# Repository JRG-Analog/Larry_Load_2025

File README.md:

# Larry_Load_2025
A current load for testing, named for the great Larry Carr, his original design.

This document describes the assembly, design, calibration and usage of “Larry Load”, a battery-powered, high accuracy current sink. The system consists of a small PCB inside and enclosure, with various panel mount components and connector mounted components to make a complete circuit.

PCB Layout is shared on OSHPark.com as LL Basic 2025.kicad_pcb

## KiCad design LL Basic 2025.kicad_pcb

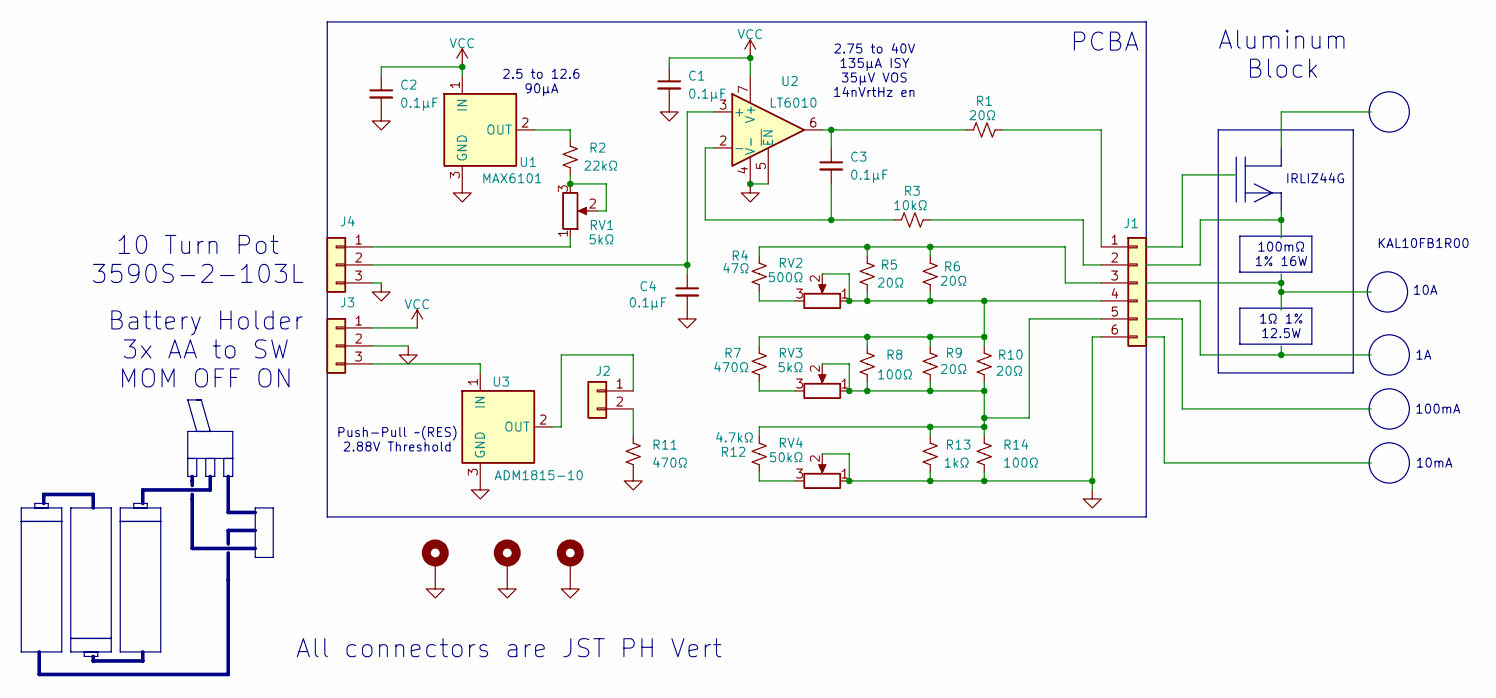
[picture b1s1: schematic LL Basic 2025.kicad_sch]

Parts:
C1, C2, C3, C4: 0.1µF; C_Rect_L4.0mm_W2.5mm_P2.50mm
H1, H2, H3: MountingHole_Pad; MountingHole_2.7mm_M2.5_DIN965_Pad
J1: Conn_01x06; JST_PH_B6B-PH-K_1x06_P2.00mm_Vertical
J2: Conn_01x02; JST_PH_B2B-PH-K_1x02_P2.00mm_Vertical
J3, J4: Conn_01x03; JST_PH_B3B-PH-K_1x03_P2.00mm_Vertical
R1, R5, R6, R9, R10: 20Ω; R_Axial_DIN0207_L6.3mm_D2.5mm_P10.16mm_Horizontal
R2: 22kΩ; R_Axial_DIN0207_L6.3mm_D2.5mm_P10.16mm_Horizontal
R3: 10kΩ; R_Axial_DIN0207_L6.3mm_D2.5mm_P10.16mm_Horizontal
R4: 47Ω; R_Axial_DIN0207_L6.3mm_D2.5mm_P10.16mm_Horizontal
R7, R11: 470Ω; R_Axial_DIN0207_L6.3mm_D2.5mm_P10.16mm_Horizontal
R8, R14: 100Ω; R_Axial_DIN0207_L6.3mm_D2.5mm_P10.16mm_Horizontal
R12: 4.7kΩ; R_Axial_DIN0207_L6.3mm_D2.5mm_P10.16mm_Horizontal
R13: 1kΩ; R_Axial_DIN0207_L6.3mm_D2.5mm_P10.16mm_Horizontal
RV1, RV3: 5kΩ; Potentiometer_Bourns_3296W_Vertical_jg
RV2: 500Ω; Potentiometer_Bourns_3296W_Vertical_jg
RV4: 50kΩ; Potentiometer_Bourns_3296W_Vertical_jg
U1: MAX6101; SOT-23
U2: LT6010; SOIC-8_3.9x4.9mm_P1.27mm
U3: ADM1815-10; SOT-23

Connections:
GND: C1.2, C2.2, C4.2, H1.1, H2.1, H3.1, J1.6, J3.2, J4.3, R11.2, R13.2, R14.2, RV4.1, RV4.2, U1.3 (GND), U2.4 (V-), U2.5 (~EN), U3.3 (GND)
unnamed: C3.1, R1.1, U2.6
unnamed: J1.1, R1.2
unnamed: J1.2, R3.2
unnamed: J1.3, R4.1, R5.1, R6.1
unnamed: J1.4, R5.2, R6.2, R7.1, R8.1, R9.1, R10.1, RV2.1, RV2.2
unnamed: J1.5, R8.2, R9.2, R10.2, R12.1, R13.1, R14.1, RV3.1, RV3.2
unnamed: J2.1, U3.2 (OUT)
unnamed: J2.2, R11.1
unnamed: J3.3, U3.1 (IN)
unnamed: J4.1, RV1.1
unnamed: C4.1, J4.2, U2.3 (+)
unnamed: R2.2, RV1.2, RV1.3
unnamed: R4.2, RV2.3
unnamed: R7.2, RV3.3
unnamed: R12.2, RV4.3
unnamed: R2.1, U1.2 (OUT)
unnamed: C3.2, R3.1, U2.2 (-)
VCC: C1.1, C2.1, J3.1, U1.1 (IN), U2.7 (V+)

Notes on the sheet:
PCBA
100mA
KAL10FB1R00
2.5 to 12.6 90µA
All connectors are JST PH Vert
Aluminum Block
Push-Pull ~(RES) 2.88V Threshold
IRLIZ44G
10mA
2.75 to 40V 135µA ISY 35µV VOS 14nVrtHz en
Battery Holder 3x AA to SW MOM OFF ON
10 Turn Pot 3590S-2-103L
100mΩ 1% 16W
10A
1Ω 1% 12.5W

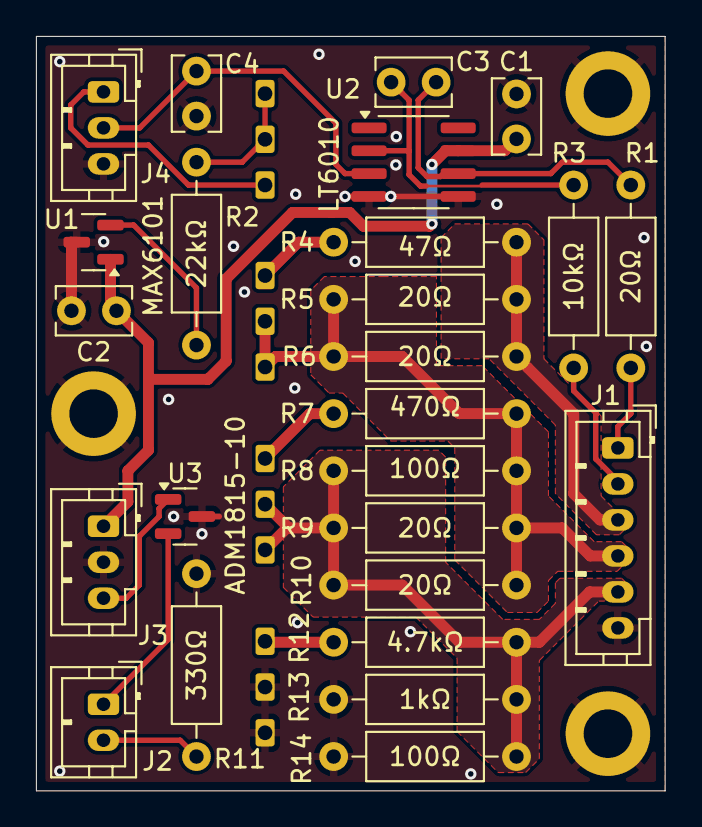
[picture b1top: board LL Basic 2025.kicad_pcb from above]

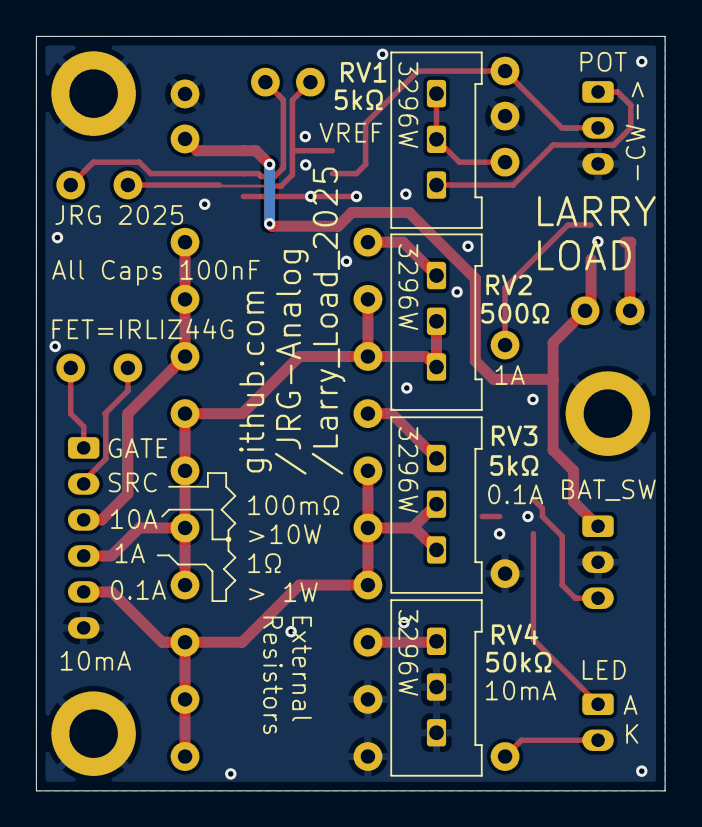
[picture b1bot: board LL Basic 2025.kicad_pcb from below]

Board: 2 copper layers, 34.9 x 41.9 mm, 32 parts (4 on the bottom side), 19 nets.
